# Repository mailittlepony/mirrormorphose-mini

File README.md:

# Mirrormorphose-mini

After a first convincing implementation of Mirrormorphose, we wanted to explore a more intimate design: a hand mirror with new features.

## Features

- Picamera compatible
- Raspberry pi compatible (now Raspberry pi zero 2w)
- Server side on the mirror
- Client side on auxiliary device
- Face morphing module
- Background removal
- Runway API module
- Face Detection module
- Modest custom trained model
- Temporary file storage in RAM disk (Linux/macOS)

## System architecture 

We developped a new architecture to do heavy tasks like background removal and face morphing while still keeping the mirror the most independent as possible. 
The portable mirror is in charge of:
- displaying and looping the AI-generated video when a gaze is detected. 
- It will also serve a simple static website to let the user upload easily his child picture.
- It then sends a picture of the user and a picture of the first frame of the AI generated video to the auxiliary device. 

The auxiliary device then:
- Removes the background of both pictures
- Generates morphing video with those pictures
- Sends it to the server

When done, the mirror will start transforming the user into himself as a child when he stares at the mirror and when he looks away it fades away.

## Design

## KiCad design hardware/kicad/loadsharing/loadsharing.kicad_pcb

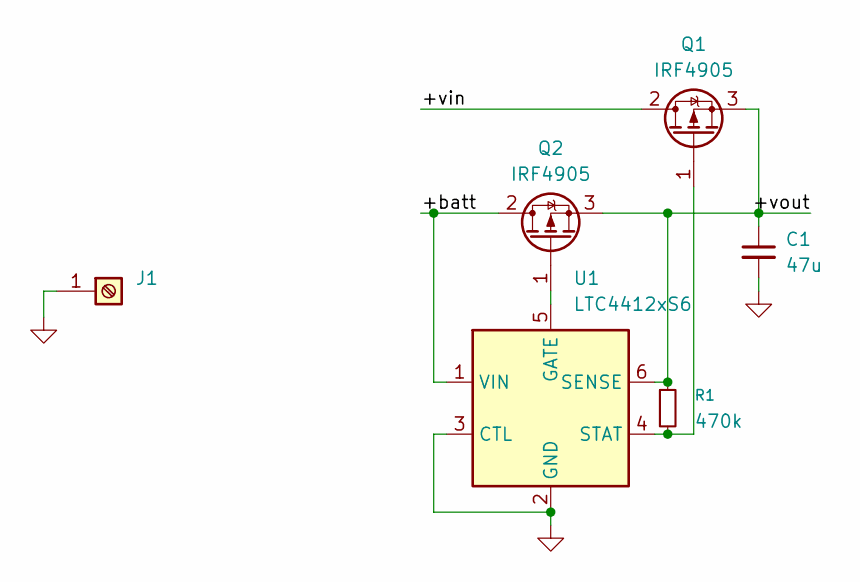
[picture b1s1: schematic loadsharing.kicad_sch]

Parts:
C1: 47u; CP_Radial_D8.0mm_P3.50mm
J1: Screw_Terminal_01x01; SolderWire-0.25sqmm_1x01_D0.65mm_OD2mm
Q1, Q2: IRF4905; TO-220-3_Vertical
R1: 470k; R_Axial_DIN0207_L6.3mm_D2.5mm_P10.16mm_Horizontal
U1: LTC4412xS6; TSOT-23-6

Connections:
/+batt: Q2.2 (D), U1.1 (VIN)
/+vin: Q1.2 (D)
/+vout: C1.1, Q1.3 (S), Q2.3 (S), R1.1, U1.6 (SENSE)
GND: C1.2, J1.1, U1.2 (GND), U1.3 (CTL)
unnamed: Q1.1 (G), R1.2, U1.4 (STAT)
unnamed: Q2.1 (G), U1.5 (GATE)

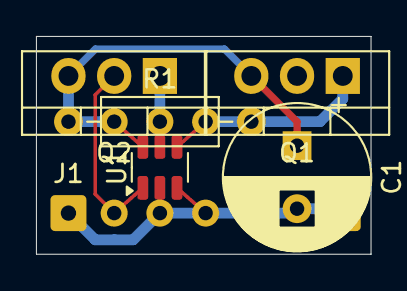
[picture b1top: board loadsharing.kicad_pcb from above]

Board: 2 copper layers, 18.6 x 12.1 mm, 6 parts (0 on the bottom side), 5 nets.

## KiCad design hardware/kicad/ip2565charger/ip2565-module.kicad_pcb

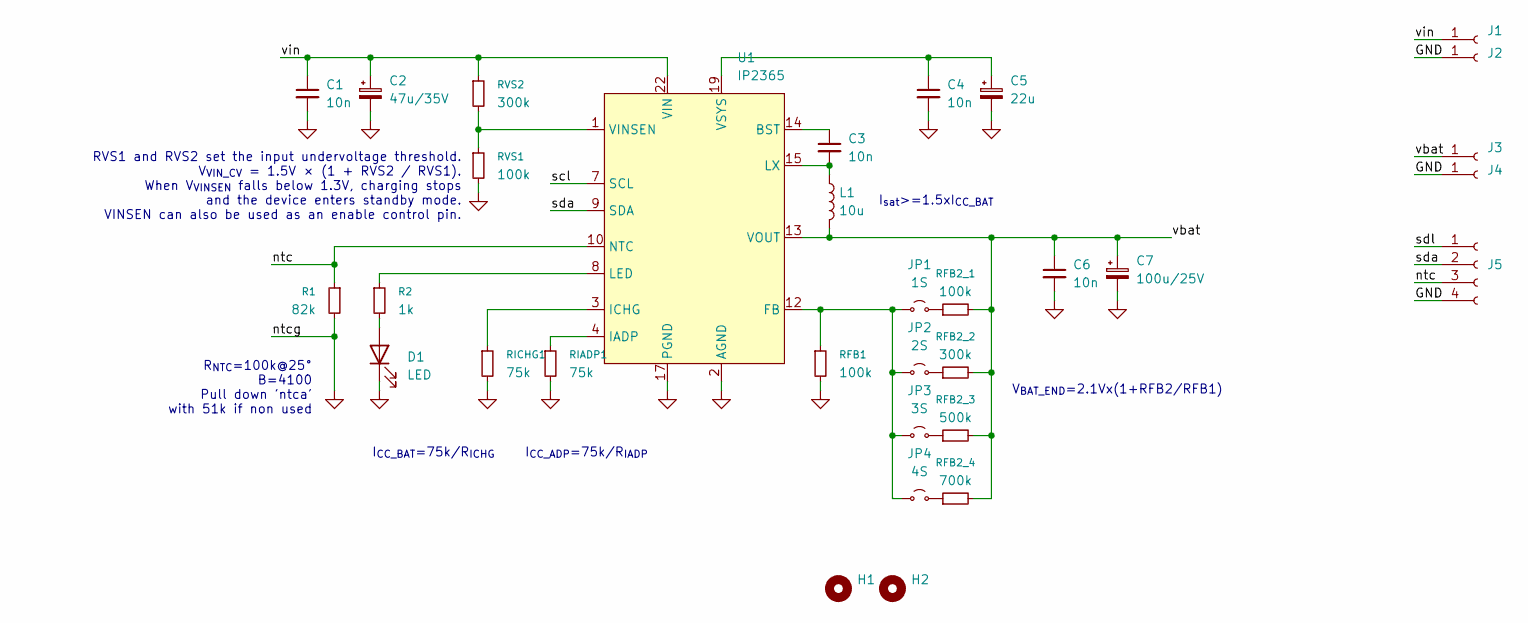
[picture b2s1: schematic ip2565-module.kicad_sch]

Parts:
C1: 10n; C_0805_2012Metric
C2: 47u/35V; CP_Elec_6.3x7.7
C3, C4, C6: 10n; C_0603_1608Metric
C5: 22u; C_0805_2012Metric
C7: 100u/25V; CP_Elec_6.3x7.7
D1: LED; LED_0603_1608Metric
H1, H2: MountingHole; MountingHole_2.5mm
J1, J2, J3, J4: SolderWire-0.75sqmm_1x01_D1.25mm_OD2.3mm
J5: PinHeader_1x04_P2.54mm_Vertical
JP1: 1S; SolderJumper-2_P1.3mm_Open_RoundedPad1.0x1.5mm
JP2: 2S; SolderJumper-2_P1.3mm_Open_RoundedPad1.0x1.5mm
JP3: 3S; SolderJumper-2_P1.3mm_Open_RoundedPad1.0x1.5mm
JP4: 4S; SolderJumper-2_P1.3mm_Open_RoundedPad1.0x1.5mm
L1: 10u; L_APV_APH1040
R1: 82k; R_0603_1608Metric
R2: 1k; R_0603_1608Metric
RFB1, RFB2_1: 100k; R_0603_1608Metric
RFB2_2: 300k; R_0603_1608Metric
RFB2_3: 500k; R_0603_1608Metric
RFB2_4: 700k; R_0603_1608Metric
RIADP1: 75k; R_0603_1608Metric
RICHG1: 75k; R_0603_1608Metric
RVS1: 100k; R_0603_1608Metric
RVS2: 300k; R_0603_1608Metric
U1: IP2365; QFN-24-1EP_4x4mm_P0.5mm_EP2.65x2.65mm_ThermalVias

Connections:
/ntc: J5.3, R1.1, U1.10 (NTC)
/scl: U1.7 (SCL)
/sda: J5.2, U1.9 (SDA)
/sdl: J5.1
/vbat: C6.1, C7.1, J3.1, L1.2, RFB2_1.2, RFB2_2.2, RFB2_3.2, RFB2_4.2, U1.13 (VOUT)
/vin: C1.1, C2.1, J1.1, RVS2.1, U1.22 (VIN), U1.23 (VIN), U1.24 (VIN)
GND: C1.2, C2.2, C4.2, C5.2, C6.2, C7.2, D1.1 (K), J2.1, J4.1, J5.4, R1.2, RFB1.2, RIADP1.2, RICHG1.2, RVS1.2, U1.2 (AGND), U1.11 (AGND), U1.17 (PGND), U1.18 (PGND), U1.25 (EPAD)
unnamed: C3.2, L1.1, U1.15 (LX), U1.16 (LX)
unnamed: C4.1, C5.1, U1.19 (VSYS), U1.20 (VSYS), U1.21 (VSYS)
unnamed: D1.2 (A), R2.2
unnamed: JP1.1 (A), JP2.1 (A), JP3.1 (A), JP4.1 (A), RFB1.1, U1.12 (FB)
unnamed: JP1.2 (B), RFB2_1.1
unnamed: JP2.2 (B), RFB2_2.1
unnamed: JP3.2 (B), RFB2_3.1
unnamed: JP4.2 (B), RFB2_4.1
unnamed: C3.1, U1.14 (BST)
unnamed: RIADP1.1, U1.4 (IADP)
unnamed: RICHG1.1, U1.3 (ICHG)
unnamed: R2.1, U1.8 (LED)
unnamed: U1.5 (NC), U1.6 (NC)
unnamed: RVS1.1, RVS2.2, U1.1 (VINSEN)

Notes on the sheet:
RVS1 and RVS2 set the input undervoltage threshold. V_{VIN_CV} = 1.5V × (1 + RVS2 / RVS1). When V_{VINSEN} falls below 1.3V, charging stops and the device enters standby mode. VINSEN can also be used as an enable control pin.
R_{NTC}=100k@25° B=4100 Pull down 'ntca' with 51k if non used
V_{BAT_END}=2.1Vx(1+RFB2/RFB1)
I_{CC_ADP}=75k/R_{IADP}
I_{CC_BAT}=75k/R_{ICHG}
I_{sat}>=1.5xI_{CC_BAT}

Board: 2 copper layers, 32 parts (0 on the bottom side), 19 nets, no tracks yet.

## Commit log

2025-06-20 Create LICENSE
2025-06-20 make basic project structure
2025-06-20 add base mirror server
2025-06-20 add client script
2025-06-20 add face-recognition script
2025-06-21 refactor and add index.html for upload
2025-06-21 add face recognition script
2025-06-21 fix face detector attribute
2025-06-21 process image
2025-06-21 fix face recognition script
2025-06-21 create ram disk script
2025-06-21 fix gen vid frame sending
2025-06-21 integrate gaze detection module
2025-06-21 modified morphing file
2025-06-21 more robust face detection with opencv tracking
2025-06-23 create draft of redme
2025-06-24 fix stuff and add setup.sh
2025-06-27 make face recognition lightweight
2025-06-27 adapt main for face detection edits
2025-06-27 fix permission for the ramdisk
2025-06-27 add basic fade api
2025-06-27 handle processing video
2025-07-03 modify auxiliary main
2025-07-03 edit camera cross-platform compatibility
2025-07-03 move overlayx lib
2025-07-03 add variable for video paths
2025-07-03 begin displaying
2025-07-03 fix omx cmd, add morph monitor
2025-07-03 use omxplayer wrapper instead of subprocess
2025-07-03 fix basename comparaison
2025-07-03 try displaying with omx+pydbus
2025-07-04 edit video class and remove dbus introspection
2025-07-04 fix dbus object path
2025-07-04 fix close fn if omx not running
2025-07-04 add vignette
2025-07-04 return fn
2025-07-04 update lib
2025-07-04 update wrapper
2025-07-04 get dbus property and fix multi omx instance/bus
2025-07-04 vignette is now optional
2025-07-04 update lib and fix res alloc check
2025-07-04 working but the transition could be better
2025-07-04 fix handler name
2025-07-04 add vignette to videos
2025-07-11 fix auxiliary part
2025-07-11 fix mirror part
2025-07-15 start fresh for a new version
2025-07-16 fix setup scripts
2025-08-06 fixed repo
2025-08-07 fixed branch
2025-08-08 add kicad pcb
2025-08-08 add bom
2025-08-29 fix structure
2025-08-29 add cad, elec, bom
2025-08-29 serve camera frame
2025-08-30 begin adapt morph
2025-08-30 fix almost morph
2025-08-30 begin implementing experience pipeline
2025-08-30 try to fix face cropping
2025-08-30 fix gaze detection + displaying
